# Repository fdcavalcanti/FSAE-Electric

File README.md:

# FSAE-Electric
Multiple designs for the Formula-E CAR

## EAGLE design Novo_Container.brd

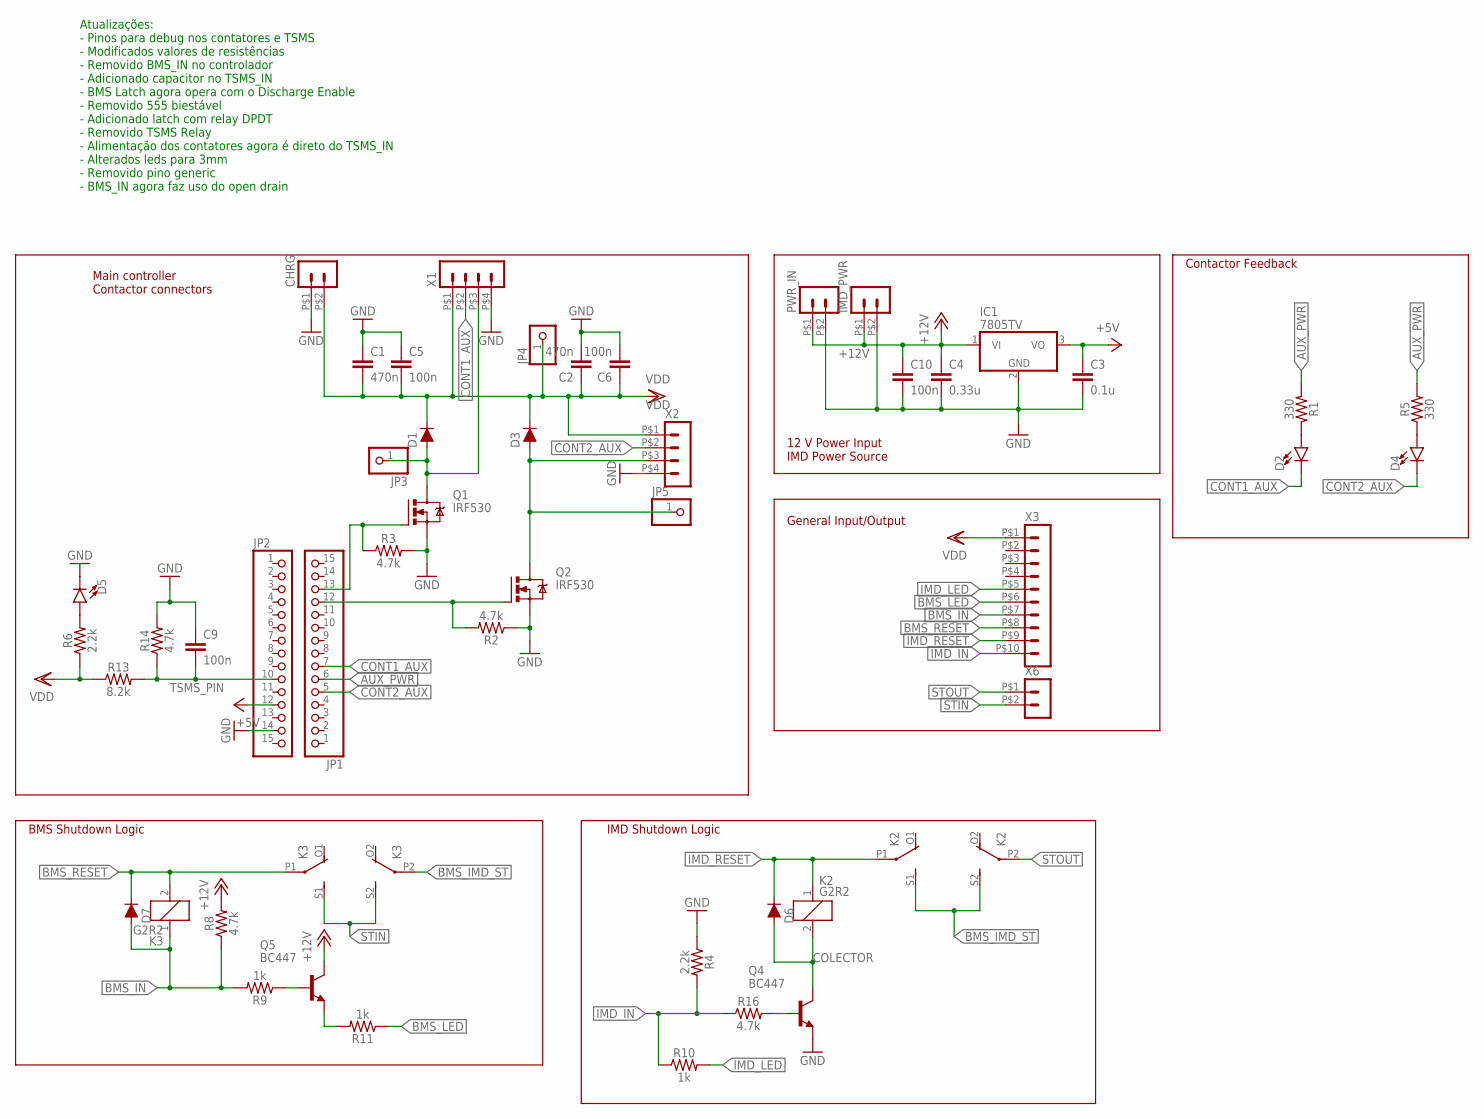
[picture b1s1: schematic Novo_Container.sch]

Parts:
C1, C2: 470n; C025-025X050
C3: 0.1u; C025-025X050
C4: 0.33u; C025-025X050
C5, C6, C9, C10: 100n; C025-025X050
CHRG: HEADER_POS2_43650-0200; 43650-0200
D1, D3, D6, D7: DIODE-1N4148
D2, D4, D5: LED3MM; LED_3MM
IC1: 7805TV; TO220V
IMD_PWR: HEADER_POS2_43650-0200; 43650-0200
JP1, JP2: PINHD-1X15; 1X15
JP3, JP4, JP5: PINHD-1X1; 1X01
K2, K3: G2R2
PWR_IN: HEADER_POS2_43650-0200; 43650-0200
Q1, Q2: IRF530; TO220BV
Q4, Q5: BC447; TO92-EBC
R1, R5: 330; AXIAL-0.3
R2, R3, R8, R14, R16: 4.7k; AXIAL-0.3
R4, R6: 2.2k; AXIAL-0.3
R9, R10, R11: 1k; AXIAL-0.3
R13: 8.2k; AXIAL-0.3
X1, X2: HEADER_POS4_43045-0401; 43045-0400
X3: HEADER_POS10_43045-1000; 43045-1000
X6: HEADER_POS2_43650-0200; 43650-0200

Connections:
+5V: C3.1, IC1.3 (VO), JP2.12
+12V: C4.1, C10.1, IC1.1 (VI), IMD_PWR.P$1 (1), PWR_IN.P$1 (1), Q5.C, R8.P$2 (2)
AUX_PWR: JP1.6, R1.P$2 (2), R5.P$2 (2)
BMS_IMD_ST: K2.S1 (S), K2.S2 (S), K3.P2
BMS_IN: D7.A, K3.1, R8.P$1 (1), R9.P$2 (2), X3.P$7 (7)
BMS_LED: R11.P$1 (1), X3.P$6 (6)
BMS_RESET: D7.C, K3.2, K3.P1, X3.P$8 (8)
COLECTOR: D6.A, K2.2, Q4.C
CONT1_AUX: D2.K (C), JP1.7, X1.P$2 (2)
CONT2_AUX: D4.K (C), JP1.5, X2.P$2 (2)
GND: C1.1, C2.2, C3.2, C4.2, C5.1, C6.2, C9.1, C10.2, CHRG.P$1 (1), D5.K (C), IC1.2 (GND), IMD_PWR.P$2 (2), JP2.14, PWR_IN.P$2 (2), Q1.S, Q2.S, Q4.E, R2.P$1 (1), R3.P$2 (2), R4.P$1 (1), R14.P$2 (2), X1.P$4 (4), X2.P$4 (4)
IMD_IN: R4.P$2 (2), R10.P$1 (1), R16.P$1 (1), X3.P$10 (10)
IMD_LED: R10.P$2 (2), X3.P$5 (5)
IMD_RESET: D6.C, K2.1, K2.P1, X3.P$9 (9)
unnamed: D5.A, R6.P$2 (2)
unnamed: D1.A, JP3.1, Q1.D, X1.P$3 (3)
unnamed: D3.A, JP5.1, Q2.D, X2.P$3 (3)
unnamed: JP1.13, Q1.G, R3.P$1 (1)
unnamed: Q5.B, R9.P$1 (1)
unnamed: JP1.12, Q2.G, R2.P$2 (2)
unnamed: Q5.E, R11.P$2 (2)
unnamed: D2.A, R1.P$1 (1)
unnamed: D4.A, R5.P$1 (1)
unnamed: Q4.B, R16.P$2 (2)
STIN: K3.S1 (S), K3.S2 (S), X6.P$2 (2)
STOUT: K2.P2, X6.P$1 (1)
TSMS_PIN: C9.2, JP2.10, R13.P$2 (2), R14.P$1 (1)
VDD: C1.2, C2.1, C5.2, C6.1, CHRG.P$2 (2), D1.C, D3.C, JP4.1, R6.P$1 (1), R13.P$1 (1), X1.P$1 (1), X2.P$1 (1), X3.P$1 (1)

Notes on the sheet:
12 V Power Input IMD Power Source
Contactor Feedback
Main controller Contactor connectors
BMS Shutdown Logic
IMD Shutdown Logic
General Input/Output
Atualizações: - Pinos para debug nos contatores e TSMS - Modificados valores de resistências - Removido BMS_IN no controlador - Adicionado capacitor no TSMS_IN - BMS Latch agora opera com o Discharge Enable - Removido 555 biestável - Adicionado latch com relay DPDT - Removido TSMS Relay - Alimentaç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

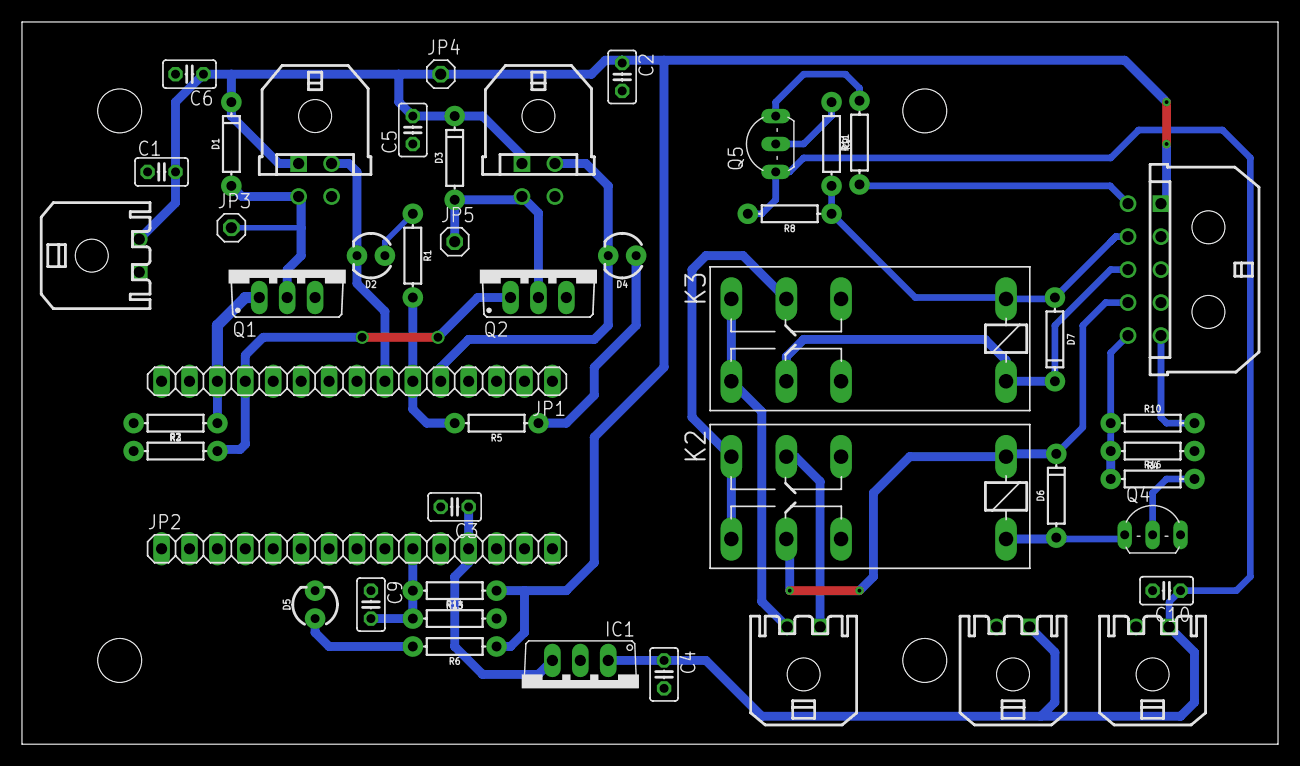
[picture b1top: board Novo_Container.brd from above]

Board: 2 copper layers, 114.3 x 65.7 mm, 47 parts (0 on the bottom side), 28 nets.

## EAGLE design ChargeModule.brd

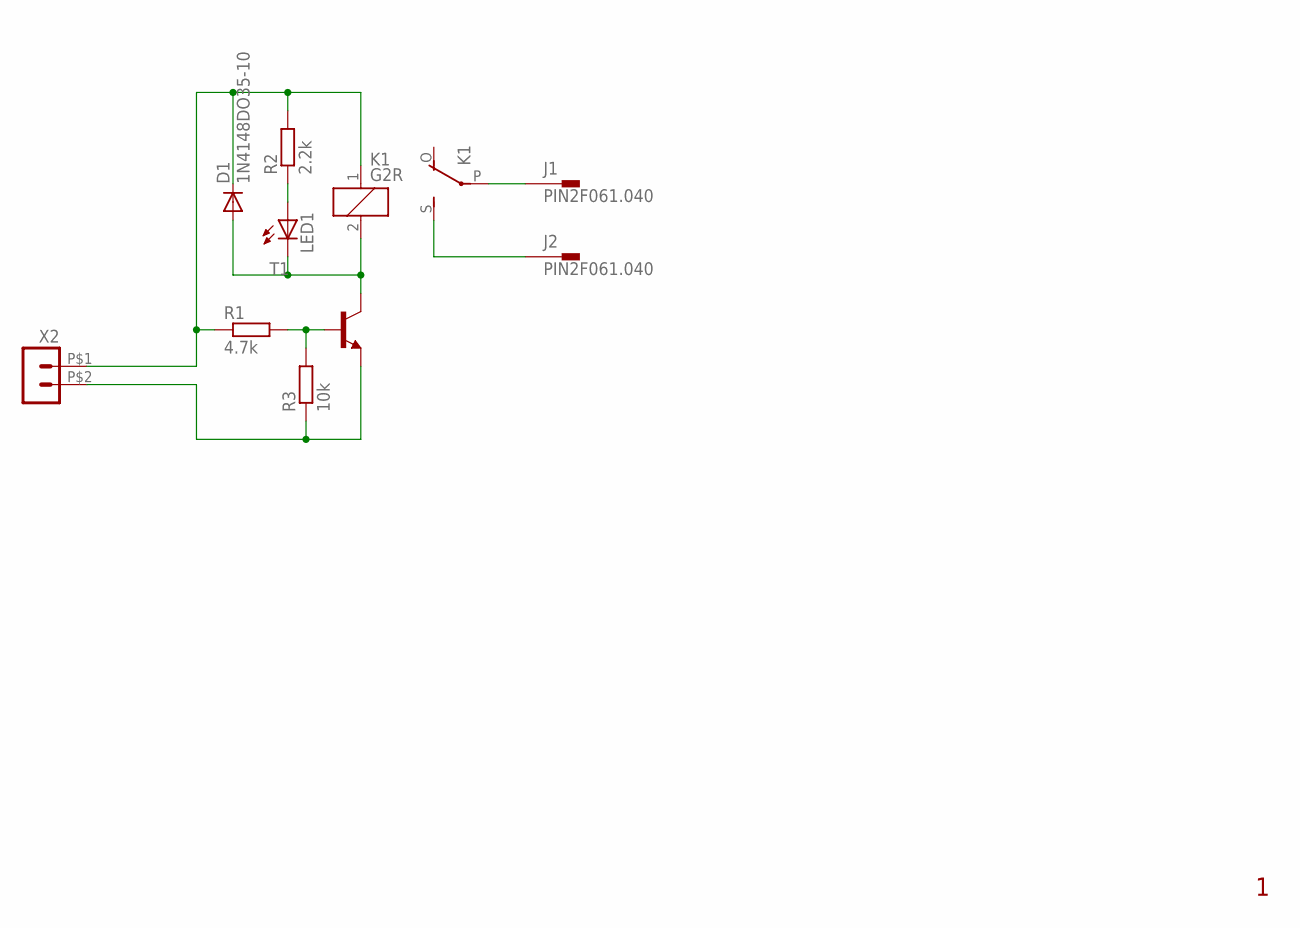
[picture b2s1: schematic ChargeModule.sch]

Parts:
D1: 1N4148DO35-10; DO35-10
J1, J2: PIN2F061.040; F061.040
K1: G2R
LED1: LED3MM
R1: 4.7k; 0207/10
R2: 2.2k; 0207/10
R3: 10k; 0207/10
T1: BC337-16-NPN-TO92-CBE; TO92-CBE
X2: HEADER_POS2_43650-0200; 43650-0200

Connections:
unnamed: R1.2, R3.2, T1.B
unnamed: D1.A, K1.2, LED1.K (C), T1.C
unnamed: J1.A1, J1.A2, K1.P
unnamed: R3.1, T1.E, X2.P$2 (2)
unnamed: LED1.A, R2.1
unnamed: D1.C, K1.1, R1.1, R2.2, X2.P$1 (1)
unnamed: J2.A1, J2.A2, K1.S

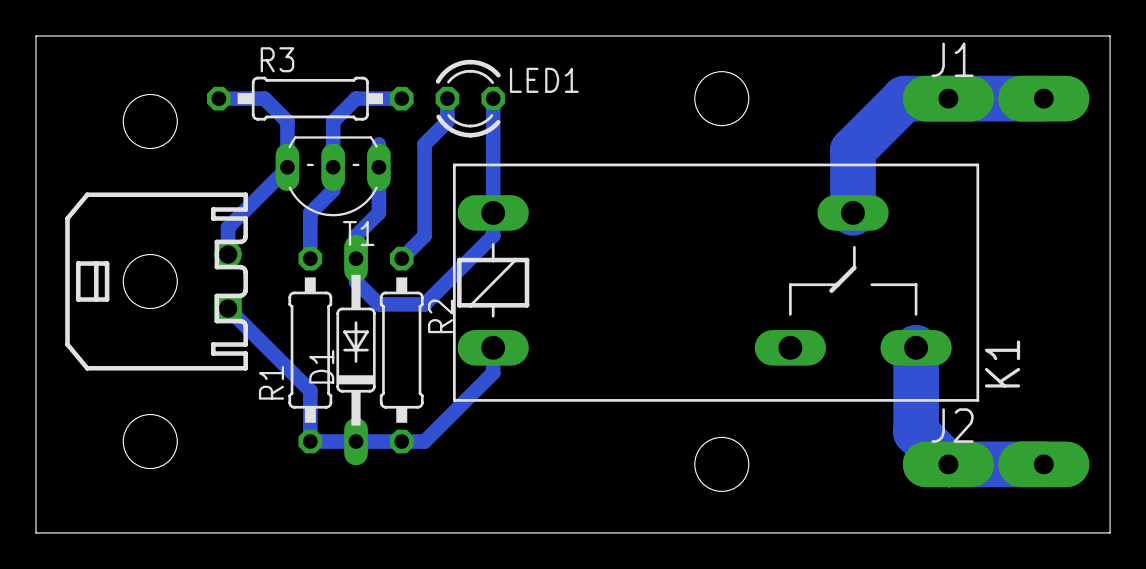
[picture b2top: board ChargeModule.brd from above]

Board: 2 copper layers, 59.7 x 27.6 mm, 10 parts (0 on the bottom side), 7 nets.

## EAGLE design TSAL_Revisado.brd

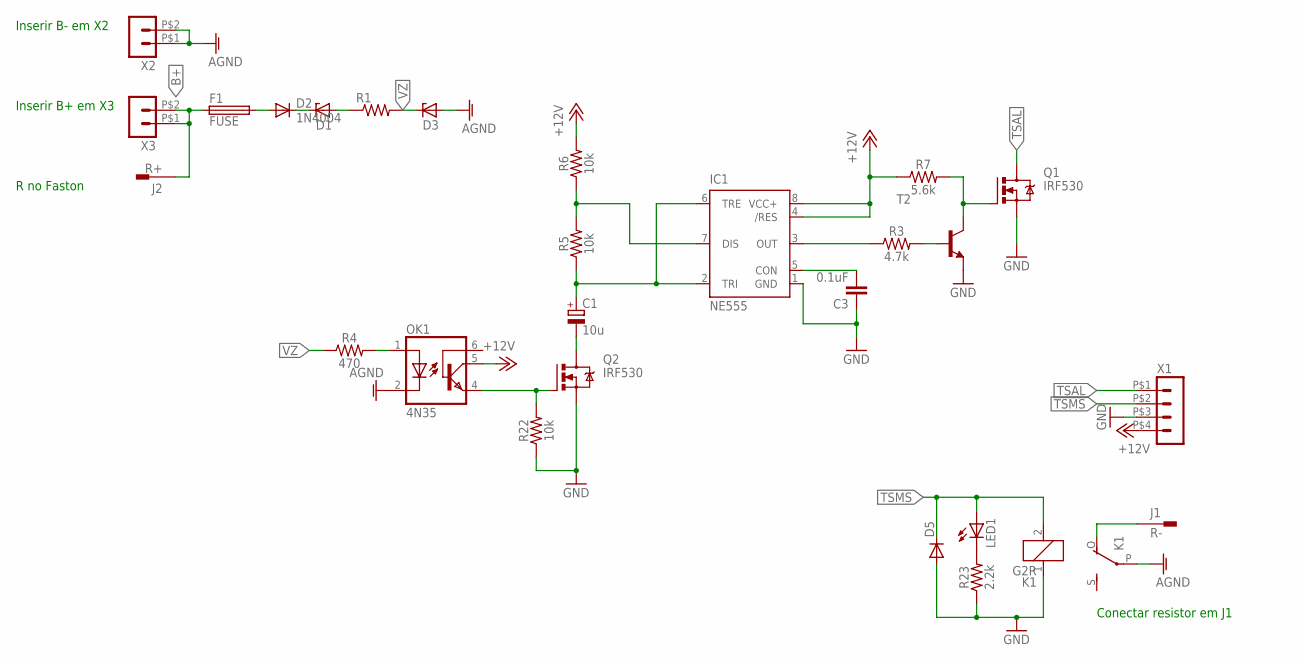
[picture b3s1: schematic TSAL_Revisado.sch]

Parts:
C1: 10u; E2-5
C3: 0.1uF; CAP-PTH-SMALL-KIT
D1, D3: ZENER-DIODEDO41Z10; DO41Z10
D2: 1N4004; DO41-10
D5: 1N4148DO35-10; DO35-10
F1: FUSE; FUSE_HOLDER_5X20MM
IC1: NE555; DIL-08
J1: R-; F061.080
J2: R+; F061.080
K1: G2R
LED1: LED3MM
OK1: 4N35; DIL06
Q1, Q2: IRF530; TO220BV
R1: R-US_0207/15; 0207/15
R3: 4.7k; AXIAL-0.3
R4: 470; AXIAL-0.3
R5, R6, R22: 10k; AXIAL-0.3
R7: 5.6k; AXIAL-0.3
R23: 2.2k; AXIAL-0.3
T2: BC337-NPN-TO92-CBE; TO92-CBE
X1: HEADER_POS4_43045-0401; 43045-0400
X2, X3: HEADER_POS2_43650-0200; 43650-0200

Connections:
+12V: IC1.4 (/RES), IC1.8 (VCC+), OK1.5 (COL), R6.P$2 (2), R7.P$1 (1), X1.P$4 (4)
AGND: D3.A, K1.P, OK1.2 (C), X2.P$1 (1), X2.P$2 (2)
B+: F1.1, J2.1A, J2.1B, X3.P$1 (1), X3.P$2 (2)
GND: C3.1, D5.A, IC1.1 (GND), K1.1, Q1.S, Q2.S, R22.P$1 (1), R23.P$1 (1), T2.E, X1.P$3 (3)
unnamed: D1.A, R1.1
unnamed: D2.A, F1.2
unnamed: J1.1A, J1.1B, K1.O
unnamed: C3.2, IC1.5 (CON)
unnamed: OK1.1 (A), R4.P$2 (2)
unnamed: IC1.3 (OUT), R3.P$1 (1)
unnamed: R3.P$2 (2), T2.B
unnamed: C1.+, IC1.2 (TRI), IC1.6 (TRE), R5.P$1 (1)
unnamed: Q1.G, R7.P$2 (2), T2.C
unnamed: IC1.7 (DIS), R5.P$2 (2), R6.P$1 (1)
unnamed: D1.C, D2.C
unnamed: C1.-, Q2.D
unnamed: OK1.4 (EMI), Q2.G, R22.P$2 (2)
unnamed: LED1.K (C), R23.P$2 (2)
TSAL: Q1.D, X1.P$1 (1)
TSMS: D5.C, K1.2, LED1.A, X1.P$2 (2)
VZ: D3.C, R1.2, R4.P$1 (1)

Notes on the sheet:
Inserir B+ em X3
R no Faston
Conectar resistor em J1
Inserir B- em X2

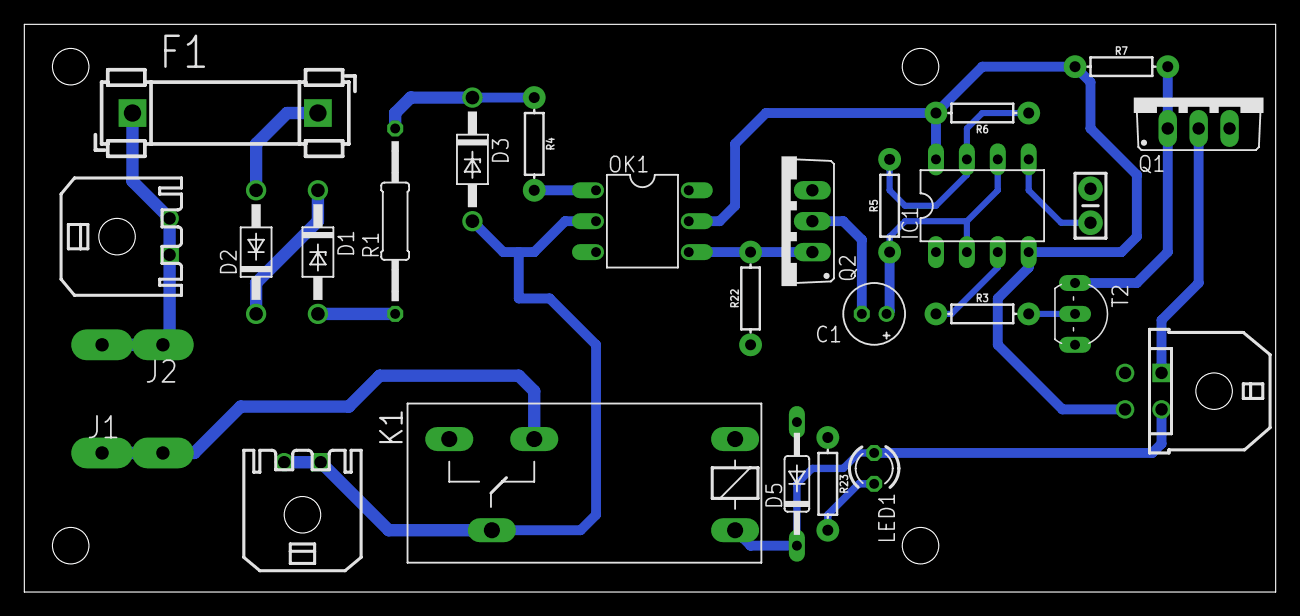
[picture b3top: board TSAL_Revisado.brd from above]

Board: 2 copper layers, 102.8 x 46.7 mm, 27 parts (0 on the bottom side), 21 nets.

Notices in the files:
parts and their libraries:
SparkFun-DiscreteSemi: Licensing: Creative Commons ShareAlike 4.0 International - https://creativecommons.org/licenses/by-sa/4.0
